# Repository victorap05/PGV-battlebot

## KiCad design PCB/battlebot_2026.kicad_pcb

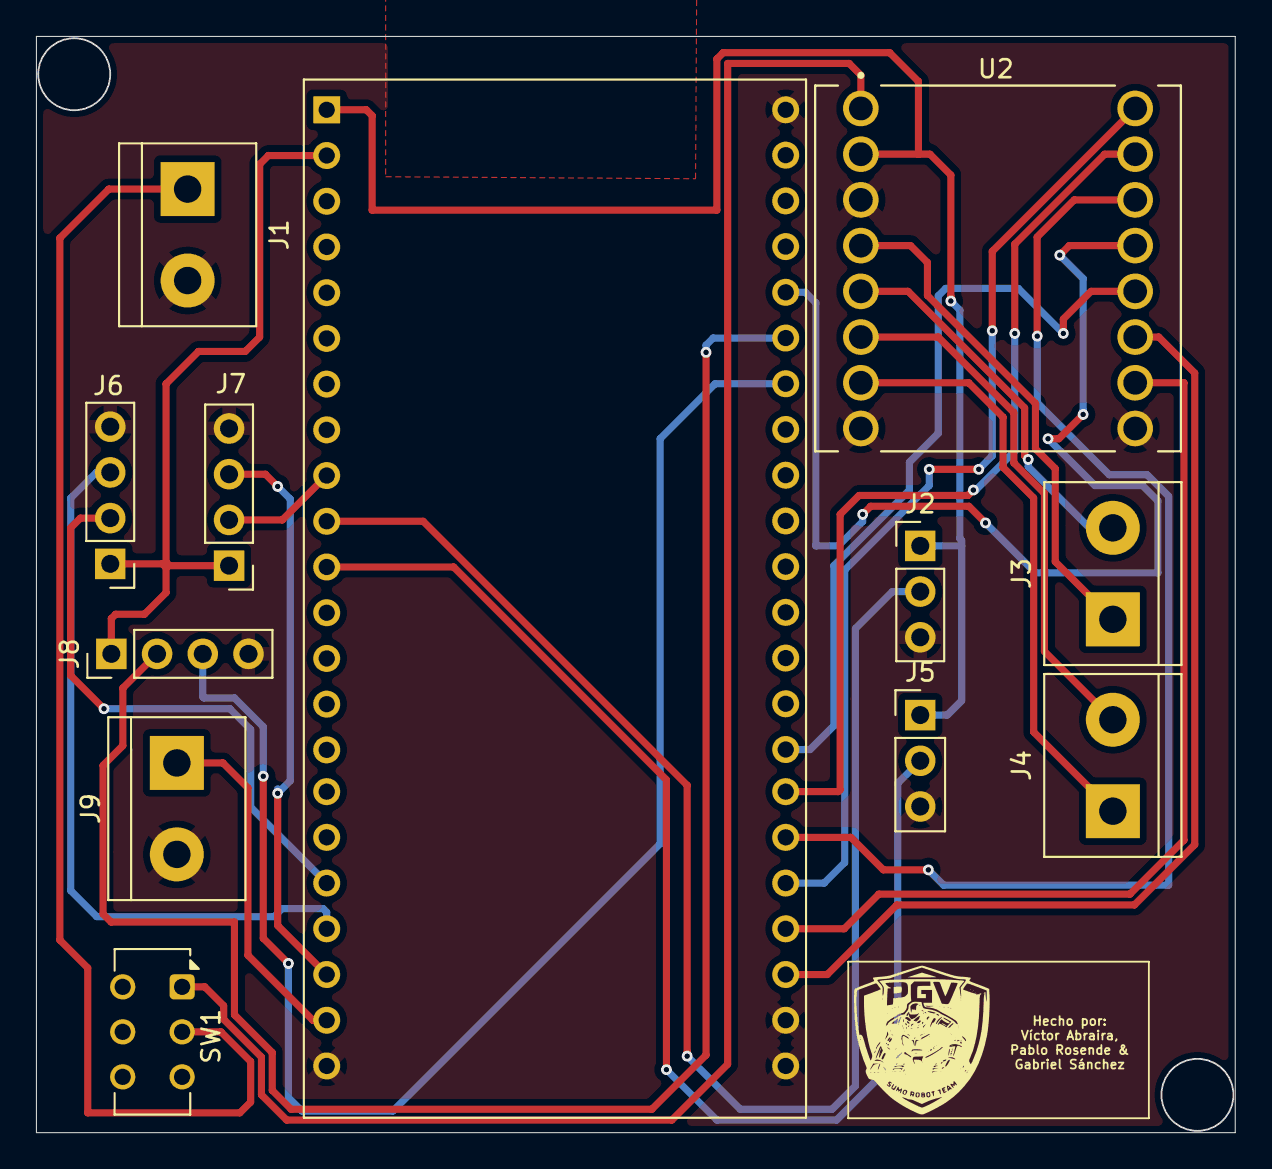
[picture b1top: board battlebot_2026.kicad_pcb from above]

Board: 2 copper layers, 66.6 x 60.9 mm, 12 parts (0 on the bottom side), 25 nets.

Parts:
J1, J3, J4, J9: Screw_Terminal_01x02; TerminalBlock_bornier-2_P5.08mm
J2, J5: Screw_Terminal_01x03; PinHeader_1x03_P2.54mm_Vertical
J6, J7, J8: Screw_Terminal_01x04; PinHeader_1x04_P2.54mm_Vertical
SW1: SW_Push; SW_CK_JS202011CQN_DPDT_Straight
U1: ESP32-S3-N8R2-DevKitM-OGT-C
U2: ROB-14450; MODULE_ROB-14450

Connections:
GND: J1.2, J2.3, J5.3, J6.4, J7.4, J8.4, J9.2, U1.22, U1.23, U1.24, U1.44, U2.3 (GND), U2.8 (GND), U2.9 (GND)
unnamed: J1.1, SW1.2
unnamed: J2.1, J5.1, U1.1, U2.2 (VCC)
unnamed: J2.2, U1.10
unnamed: J3.1, U2.4 (A01)
unnamed: J3.2, U2.5 (A02)
unnamed: J4.1, U2.7 (B01)
unnamed: J4.2, U2.6 (B02)
unnamed: J5.2, U1.11
unnamed: J6.1, J7.1, J8.1, U1.2
unnamed: J6.2, U1.18
unnamed: J6.3, U1.19
unnamed: J7.2, U1.9
unnamed: J7.3, U1.20
unnamed: J8.2, U1.39
unnamed: J8.3, U1.38
unnamed: J9.1, U1.21
unnamed: U1.40, U2.13 (STBY)
unnamed: U1.25, U2.11 (BI2)
unnamed: U1.26, U2.10 (PWMB)
unnamed: U1.27, U2.16 (PWMA)
unnamed: U1.30, U2.12 (BI1)
unnamed: U1.28, U2.14 (AI1)
unnamed: U1.29, U2.15 (AI2)
unnamed: SW1.1, U2.1 (VM)
